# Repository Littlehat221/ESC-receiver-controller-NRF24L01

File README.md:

# ESC-receiver-controller-NRF24L01
Receiver and controller(transmitter) for electronic speed controllers. Designed using NRF24L01 transceiver

Specs
- 4 PWM signals plus one digital signal
- Utilizes:
  - 2 joysticks
  - 4 tactile buttons
  - 2 potentiometers
  - 2 toggle swiches
TODO:
- include BOM
- HOWTO guide
- Provide cleaned up code for receiver and controller

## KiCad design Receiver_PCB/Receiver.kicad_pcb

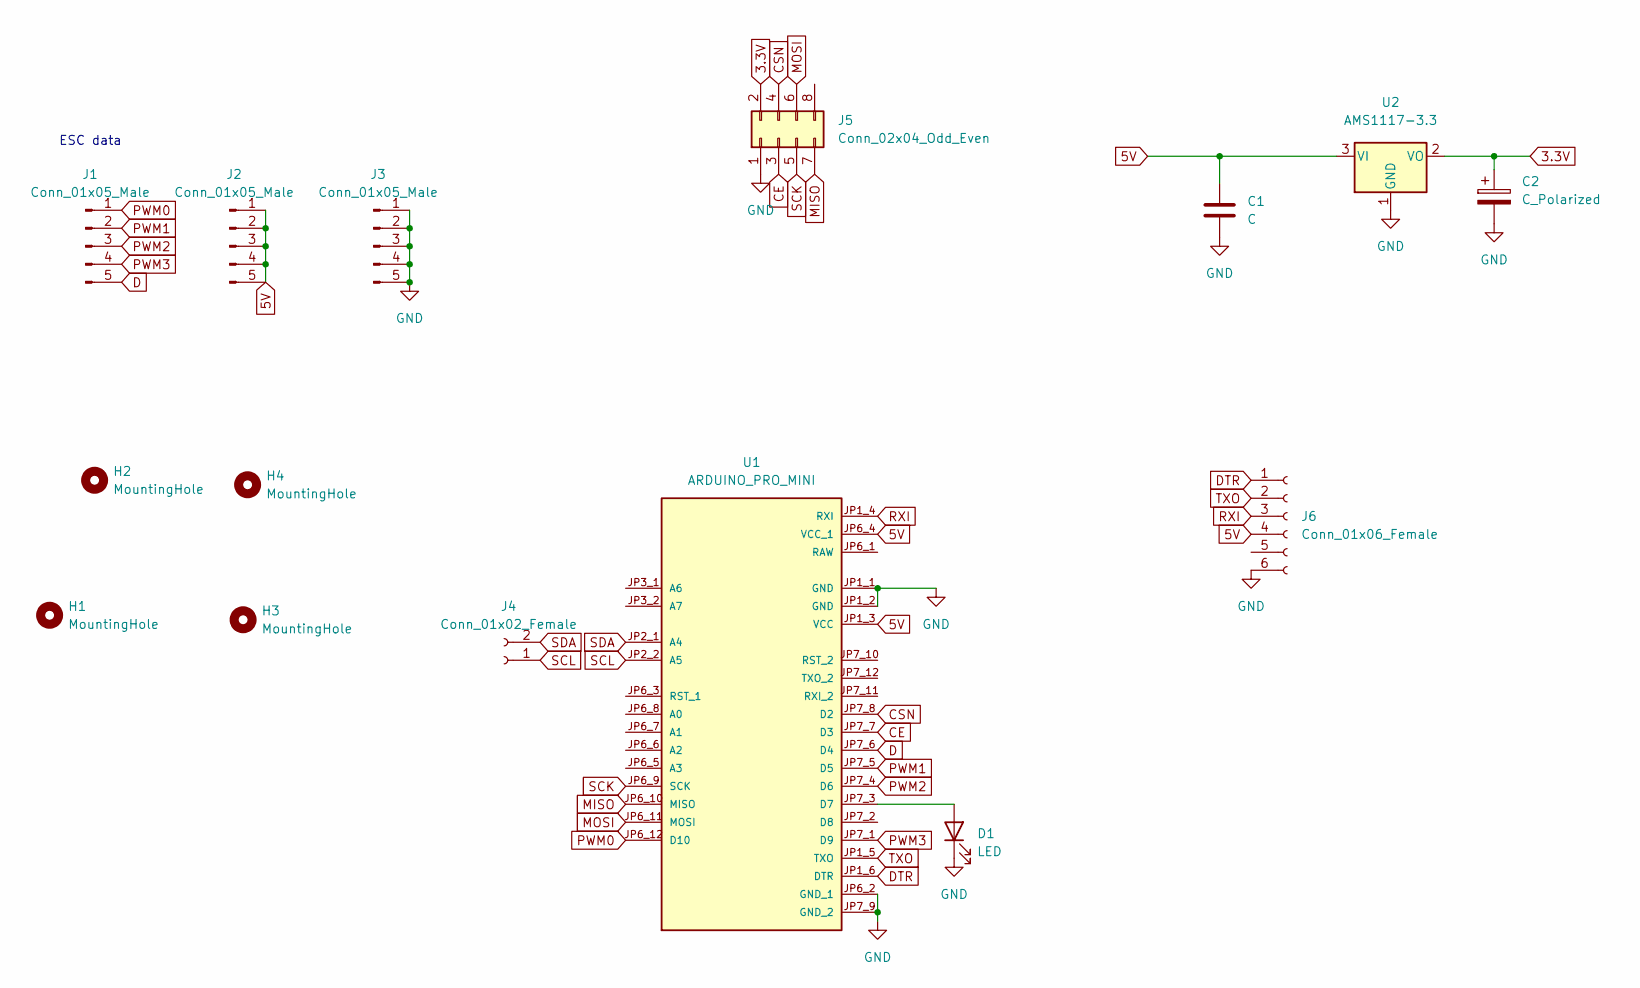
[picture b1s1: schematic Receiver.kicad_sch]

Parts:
C1: C; C_Disc_D5.1mm_W3.2mm_P5.00mm
C2: C_Polarized; CP_Radial_D5.0mm_P2.00mm
D1: LED; LED_D5.0mm
H1, H2, H3, H4: MountingHole; MountingHole_2mm
J1, J2, J3: Conn_01x05_Male; PinHeader_1x05_P2.54mm_Vertical
J4: Conn_01x02_Female; PinHeader_1x02_P2.54mm_Vertical
J5: Conn_02x04_Odd_Even; PinHeader_2x04_P2.54mm_Vertical
J6: Conn_01x06_Female; PinHeader_1x06_P2.54mm_Vertical
U1: ARDUINO_PRO_MINI; MODULE_ARDUINO_PRO_MINI; PARTREV N/A
U2: AMS1117-3.3; SOT-223-3_TabPin2

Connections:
3.3V: C2.1, J5.2, U2.2 (VO)
5V: C1.1, J2.1, J2.2, J2.3, J2.4, J2.5, J6.4, U1.JP1_3 (VCC), U1.JP6_4 (VCC_1), U2.3 (VI)
CE: J5.3, U1.JP7_7 (D3)
CSN: J5.4, U1.JP7_8 (D2)
D: J1.5, U1.JP7_6 (D4)
DTR: J6.1, U1.JP1_6 (DTR)
GND: C1.2, C2.2, D1.1 (K), J3.1, J3.2, J3.3, J3.4, J3.5, J5.1, J6.6, U1.JP1_1 (GND), U1.JP1_2 (GND), U1.JP6_2 (GND_1), U1.JP7_9 (GND_2), U2.1 (GND)
MISO: J5.7, U1.JP6_10 (MISO)
MOSI: J5.6, U1.JP6_11 (MOSI)
unnamed: D1.2 (A), U1.JP7_3 (D7)
PWM0: J1.1, U1.JP6_12 (D10)
PWM1: J1.2, U1.JP7_5 (D5)
PWM2: J1.3, U1.JP7_4 (D6)
PWM3: J1.4, U1.JP7_1 (D9)
RXI: J6.3, U1.JP1_4 (RXI)
SCK: J5.5, U1.JP6_9 (SCK)
SCL: J4.1, U1.JP2_2 (A5)
SDA: J4.2, U1.JP2_1 (A4)
TXO: J6.2, U1.JP1_5 (TXO)

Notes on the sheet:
ESC data

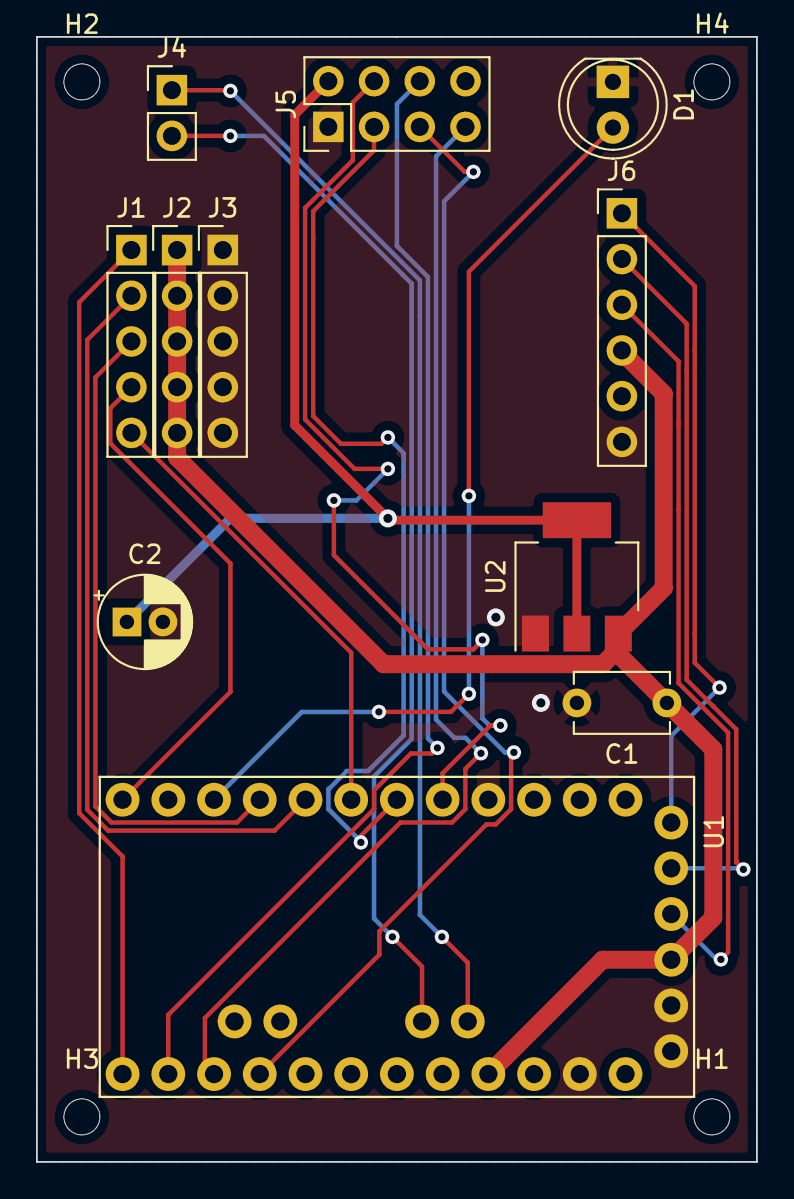
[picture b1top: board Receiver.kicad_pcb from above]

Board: 2 copper layers, 40.0 x 62.5 mm, 15 parts (0 on the bottom side), 19 nets.

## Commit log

2023-01-30 Delete Receiver_PCB directory
    Old + bad files
2023-01-30 Add files via upload
    New 2.0 versions of receiver and controller PCB.
2023-01-30 Update README.md
    Added description for 2.0.
